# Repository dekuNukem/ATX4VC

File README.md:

# ATX4VC: ATX Power on Retro Computers!

[Buy ATX4VC](https://www.tindie.com/products/dekuNukem/atx4vc-atx-power-on-retro-computers/) | [Discord](https://discord.gg/T9uuFudg7j) | [User Manual](#user-manual) | [Table of Contents](#Table-of-Contents)

ATX4VC lets you **use ATX power supply on vintage computers**.

* Plug in ATX PSU on one end
* Get 12V, 5V, 3.3V, -12V, -5V out the other!

Features:

* All common voltage rails: +12V, +5V, +3.3V, -5V, -12V.
	* Also `5V Standby` and `Power-Good`
* Toolless Lever-Actuated Terminal Block
* USB-C Power Output
* 2x PC Fan Headers

You can use ATX4VC to:

* Replace retro computer PSUs
* Test and diagnose vintage hardware
* As general-purpose multi-voltage bench PSU

## Get ATX4VC

[Click me to get one!](https://www.tindie.com/products/dekuNukem/atx4vc-atx-power-on-retro-computers/)

## PicoRC

Also [check out PicoRC](https://picorc.com) for **device-specific** and **lower-cost** PicoPSU adaptors.

## Showcase

Here ATX4VC replaces the dead PSU in my IBM 5155 Portable PC, providing +12, +5, -12, and -5V.

Note the significant simplification and space/weight saving.

It also works as a **multi-voltage bench PSU** for testing and diagnostics.

Here it powers a Macintosh Plus motherboard with +12, +5, and -12V.

## Why

Power supplies are a major failure point of old computers today.

Those early PSUs are heavy, inefficient, and (slightly) explosive! After 40 odd years, many are not working, or worse might cause damage with out-of-spec voltages.

ATX4VC is designed to replace them with much more reliable modern ATX PSUs, and help test and diagnose vintage computers.

## User Manual

### ATX vs Pico PSU

ATX4VC works with **any ATX PSU**.

Although for **permanent retrofitting**, a **PicoPSU** is recommended due to its compact size.

* [Official website](https://www.mini-box.com/DC-DC) and [distributors](https://www.mini-box.com/site/resellers.html)
    * The cheapest **80W** one should be plenty for most
    * The **160W** variant is recommended if using many expansion cards and/or **spinning hard drive**
* Avoid **generic clones**
    * They over-rate and are of low quality
* A power brick with **12V DC** and **center positive** 5.5x2.5mm barrel jack is also needed.
    * They are very popular and you might already have one
    * Make sure it has enough wattage

### Quick Start

* Don't connect any load yet!

1. Plug in ATX connector
2. On **Power Mode** switch, select **Soft Power** (left position).
3. Press the button

PSU should turn on, voltage rail LEDs should light up. 

That's the gist of it! **Please do keep reading** for more info.

### Power Modes

* Soft Power
    * **Short press** once to turn on
    * Short press again to turn off
    * Suitable for **momentary push buttons**
* Hard Power
    * **Hold down** to power on
    * **Release** to power off
    * Suitable for **latching buttons / flip switches**
    * Connected directly to ATX **PS_ON** Signal

### External Power Button and Power LED

You can also attach an **external power button** and **power LED** to the headers below:

* Note LED polarity
* LED header has built-in **330 Ohm** resistor 
* Select suitable power mode
    * Soft Power: Momentary Pushbuttons
    * Hard Power: Latching Buttons / Flip Switches

### Power Connection

* See photo for power rails
    * For aux output harness, use **8P JST VH 3.96** female connector.
* 5VSB = 5V Standby
    * Available even when PSU is off
* Power Good Signal
    * 5V when all rails are stable
    * 0V otherwise

To connect a wire:

* Strip the insulation about 12mm / 0.5in.
* Lift handle, insert, push back down.

Also, make sure the conductor is thick enough!

Label the rails, vinyl stickers are available on the [product page](https://www.tindie.com/products/dekuNukem/atx4vc-atx-power-on-retro-computers/):

### Pre-flight Checks

Before powering up:

* Double check the **correct voltage terminal** is used
* Check for **dead shorts** between each voltage rail and GND, and between themselves!

Once powered up:

* Check voltage readings on each rail

Remember that ATX4VC **DOES NOT** monitor or condition voltage rails, so ensure the PSU itself is of good quality and trustworthy!

### Current Limit

* **`5 AMPS MAX`** OVER **ANY SINGLE RAIL**
* **`7 AMPS MAX`** **TOTAL CURRENT** OVER ALL RAILS

If more is needed, **tap the power directly** from a Molex connector.

See your PSU label or datasheet to see how much current it can provide:

### Fuses

* USE FUSES RATED **5A OR LESS**
* **DO NOT BYPASS FUSES**

ATX4VC uses common **automotive fuses**.

Regular, Mini, and Low-profile Mini all work.

Simply push into the holder.

### Fan Headers

Two PC Fan headers are available. You can plug in any regular **12V PC fan**, both 3-Pin and 4-Pin.

### USB-C Power Output

An USB-C port is available for **powering external devices**.

* **OUTPUT ONLY**, **DO NOT BACKFEED** with another powered device.

## Questions or Comments?

Feel free to ask in official [Discord Chatroom](https://discord.gg/T9uuFudg7j), raise a [Github issue](https://github.com/dekuNukem/ATX4VC/issues), or email `dekunukem` `gmail.com`!

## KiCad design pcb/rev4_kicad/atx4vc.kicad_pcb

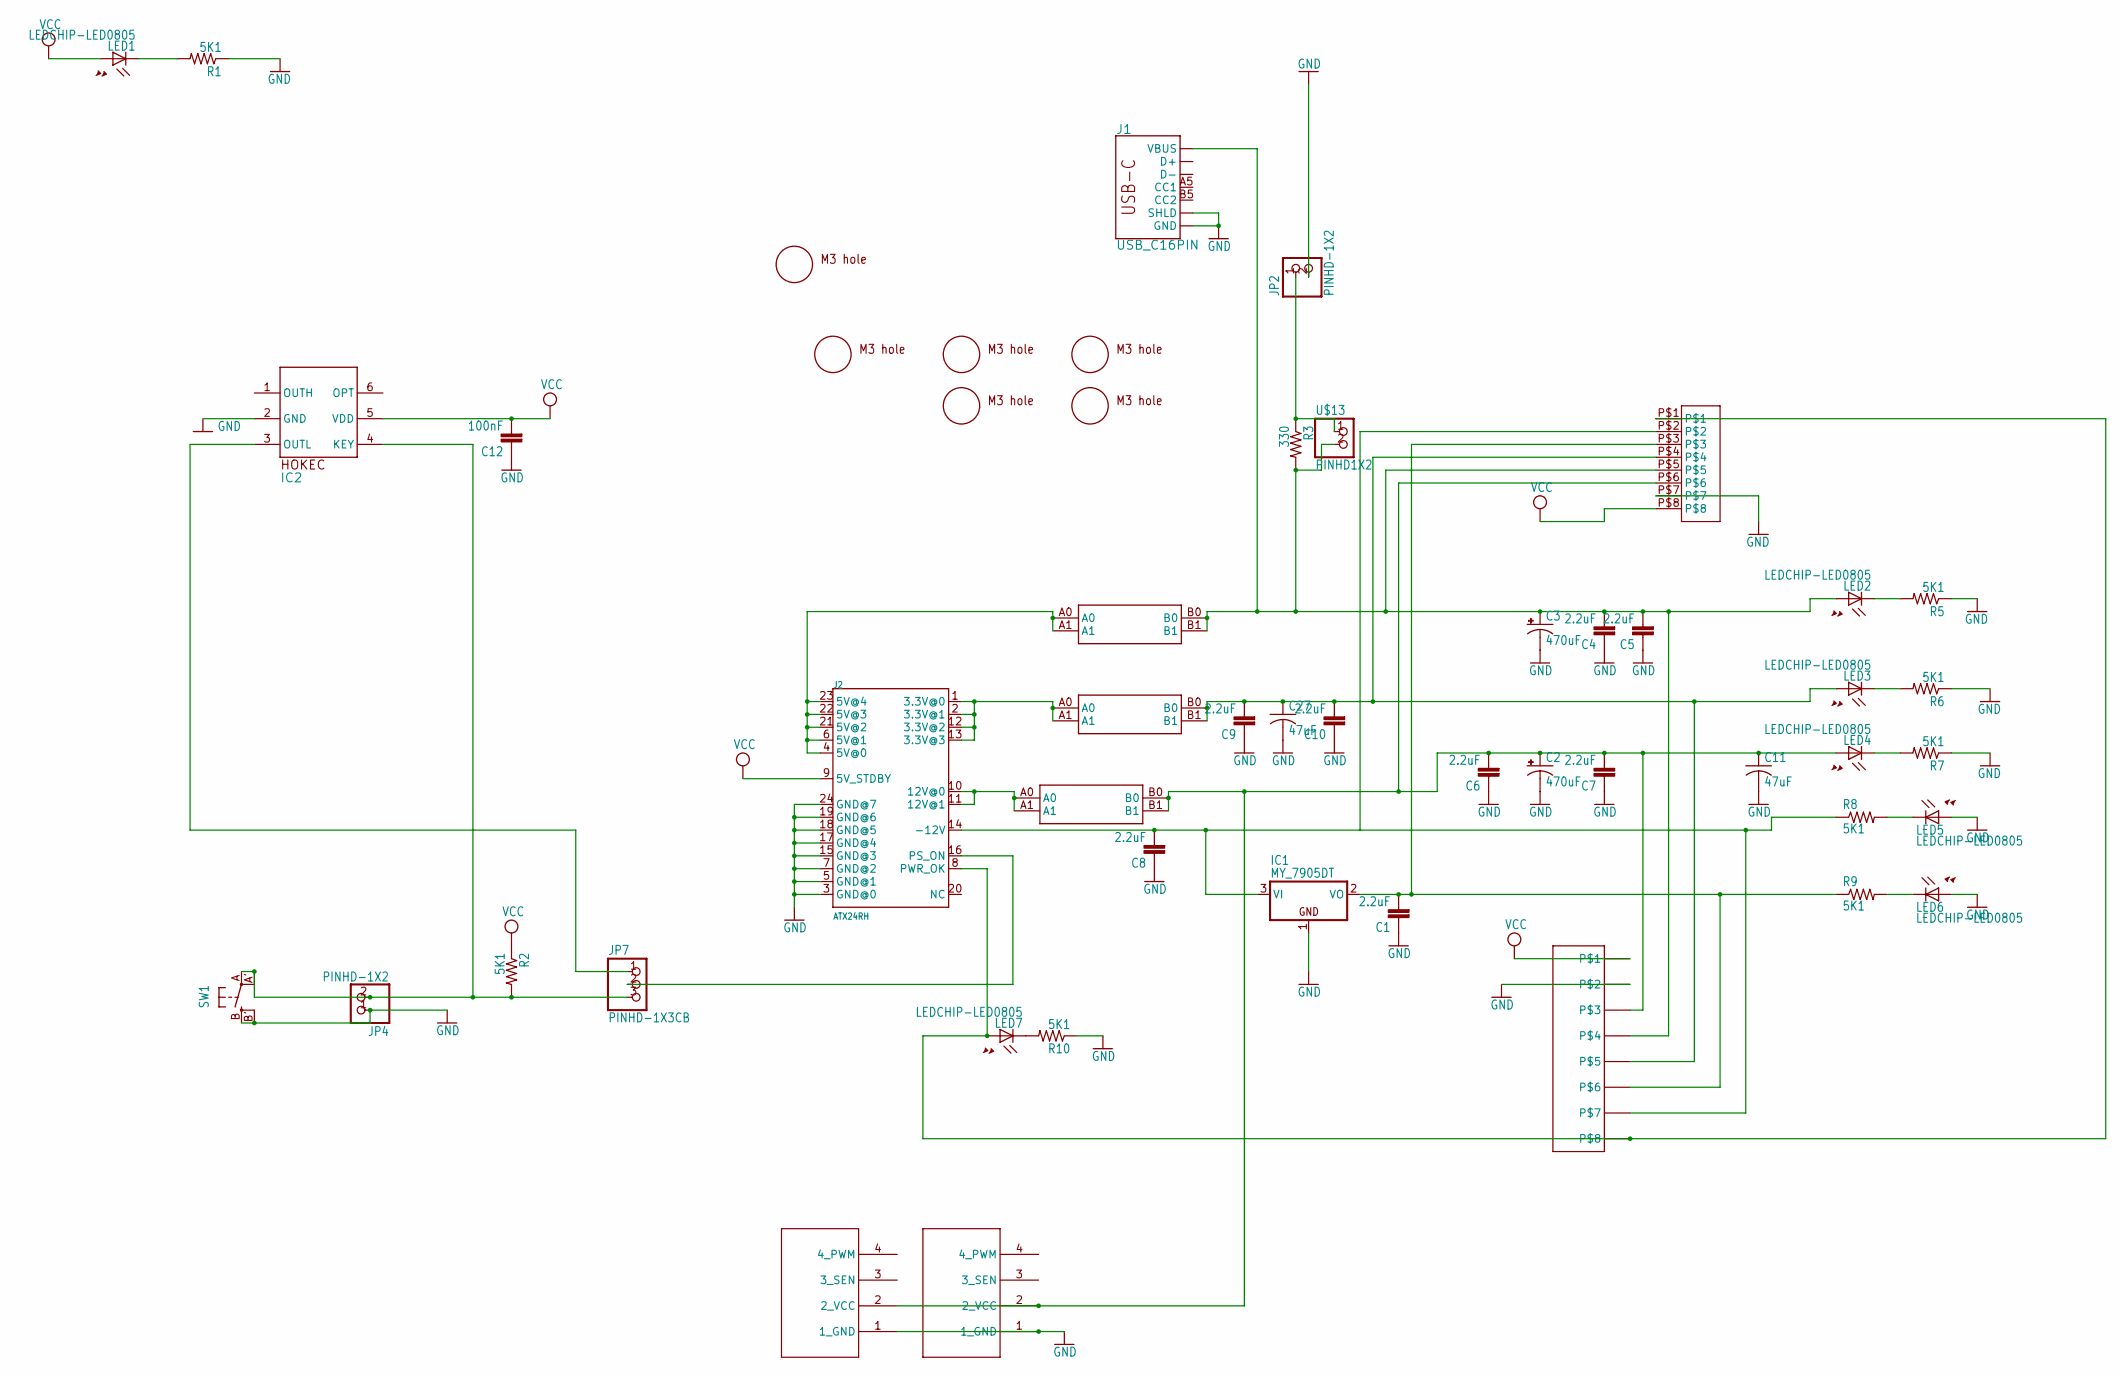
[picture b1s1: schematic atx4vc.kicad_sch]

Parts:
C1, C4, C5, C6, C7, C8, C9, C10: 2.2uF; 0805$1
C2, C3: 470uF; SMC_D
C11, C27: 47uF; C1210
C12: 100nF; 0805$1
IC1: MY_7905DT; ADAFRUIT_TO252
IC2: MAX486X/SOT; SOT23-6
J1: USB_C16PIN; USB-C-16P
J2: ATX24RH; ATX24_RIGHT_ANGLE
JP1, JP5: 4PIN_FAN; 1X04
JP2, JP4: PINHD-1X2; 1X02
JP7: PINHD-1X3CB; 1X03-CLEANBIG
LED1, LED2, LED3, LED4, LED5, LED6, LED7: LEDCHIP-LED0805; CHIP-LED0805
R1, R2, R5, R6, R7, R8, R9, R10: 5K1; 0805
R3: 330; 0805
SW1: SPST_TACT-EVQQ2; EVQ-Q2
U$1, U$2, U$3, U$4, U$5, U$6: M3_MOUNTING_HOLE; M3_MOUNTING_HOLE_PACK
U$7: 396_CONN_VH396_8P; 396_CONN_396_8P
U$9, U$10, U$11: CAR_FUSE_HOLDER3IN1; FUSE_HOLDER_3IN1
U$12: DG2204R-5.0-8DG2204-8; DG2204R-8
U$13: PINHD1X2; 1X02

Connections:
GND: C1.1, C2.-, C3.-, C4.1, C5.1, C6.1, C7.1, C8.1, C9.1, C10.1, C11.2, C12.1, C27.2, IC1.1 (GND), IC2.2 (GND), J1.GND, J1.GND2 (GND), J1.SHLD1 (SHLD), J1.SHLD2 (SHLD), J1.SHLD3 (SHLD), J1.SHLD4 (SHLD), J1.SHLD5 (SHLD), J1.SHLD6 (SHLD), J1.SHLD7 (SHLD), J1.SHLD8 (SHLD), J2.3 (GND@0), J2.5 (GND@1), J2.7 (GND@2), J2.15 (GND@3), J2.17 (GND@4), J2.18 (GND@5), J2.19 (GND@6), J2.24 (GND@7), JP1.1 (1_GND), JP2.2, JP4.1, JP5.1 (1_GND), LED5.A, LED6.A, R1.1, R5.1, R6.1, R7.1, R10.1, SW1.B (S), SW1.B' (S1), U$7.P$7, U$12.P$3, U$12.P$4
unnamed: C3.+, C4.2, C5.2, J1.VBUS1 (VBUS), J1.VBUS2 (VBUS), LED2.A, R3.2, U$7.P$5, U$9.B0, U$9.B1, U$12.P$7, U$12.P$8, U$13.2
unnamed: C9.2, C10.2, C27.1, LED3.A, U$7.P$4, U$10.B0, U$10.B1, U$12.P$9, U$12.P$10
unnamed: C8.2, IC1.3 (VI), J2.14 (-12V), R8.1, U$7.P$2, U$12.P$13, U$12.P$14
unnamed: C1.2, IC1.2 (VO), R9.1, U$7.P$3, U$12.P$11, U$12.P$12
unnamed: IC2.4 (KEY), JP4.2, JP7.3, R2.2, SW1.A, SW1.A' (P1)
unnamed: IC2.3 (OUTL), JP7.1
unnamed: J1.A6 (D+), J1.B6 (D+)
unnamed: J1.A7 (D-), J1.B7 (D-)
unnamed: J2.1 (3.3V@0), J2.2 (3.3V@1), J2.12 (3.3V@2), J2.13 (3.3V@3), U$10.A0, U$10.A1
unnamed: J2.4 (5V@0), J2.6 (5V@1), J2.21 (5V@2), J2.22 (5V@3), J2.23 (5V@4), U$9.A0, U$9.A1
unnamed: J2.10 (12V@0), J2.11 (12V@1), U$11.A0, U$11.A1
unnamed: J2.16 (PS_ON), JP7.2
unnamed: J2.8 (PWR_OK), LED7.A, U$7.P$1, U$12.P$15, U$12.P$16
unnamed: C2.+, C6.2, C7.2, C11.1, JP1.2 (2_VCC), JP5.2 (2_VCC), LED4.A, U$7.P$6, U$11.B0, U$11.B1, U$12.P$5, U$12.P$6
unnamed: JP2.1, R3.1, U$13.1
unnamed: LED1.C, R1.2
unnamed: LED2.C, R5.2
unnamed: LED3.C, R6.2
unnamed: LED4.C, R7.2
unnamed: LED5.C, R8.2
unnamed: LED6.C, R9.2
unnamed: LED7.C, R10.2
VCC: C12.2, IC2.5 (VDD), J2.9 (5V_STDBY), LED1.A, R2.1, U$7.P$8, U$12.P$1, U$12.P$2

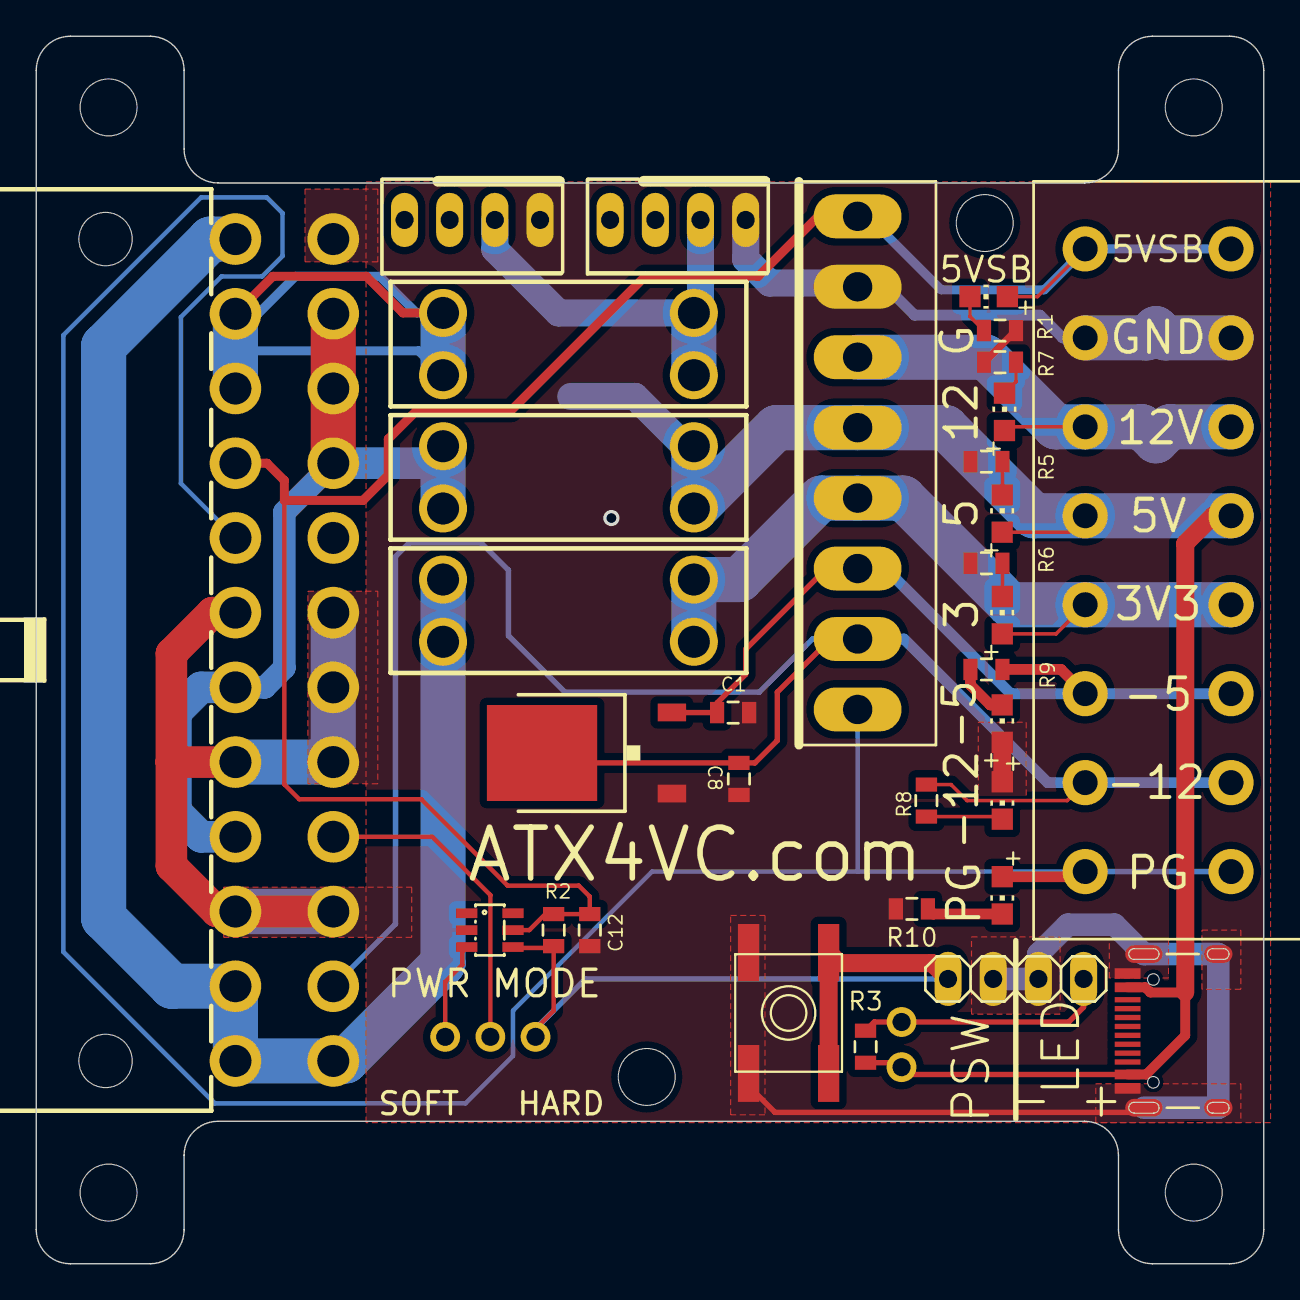
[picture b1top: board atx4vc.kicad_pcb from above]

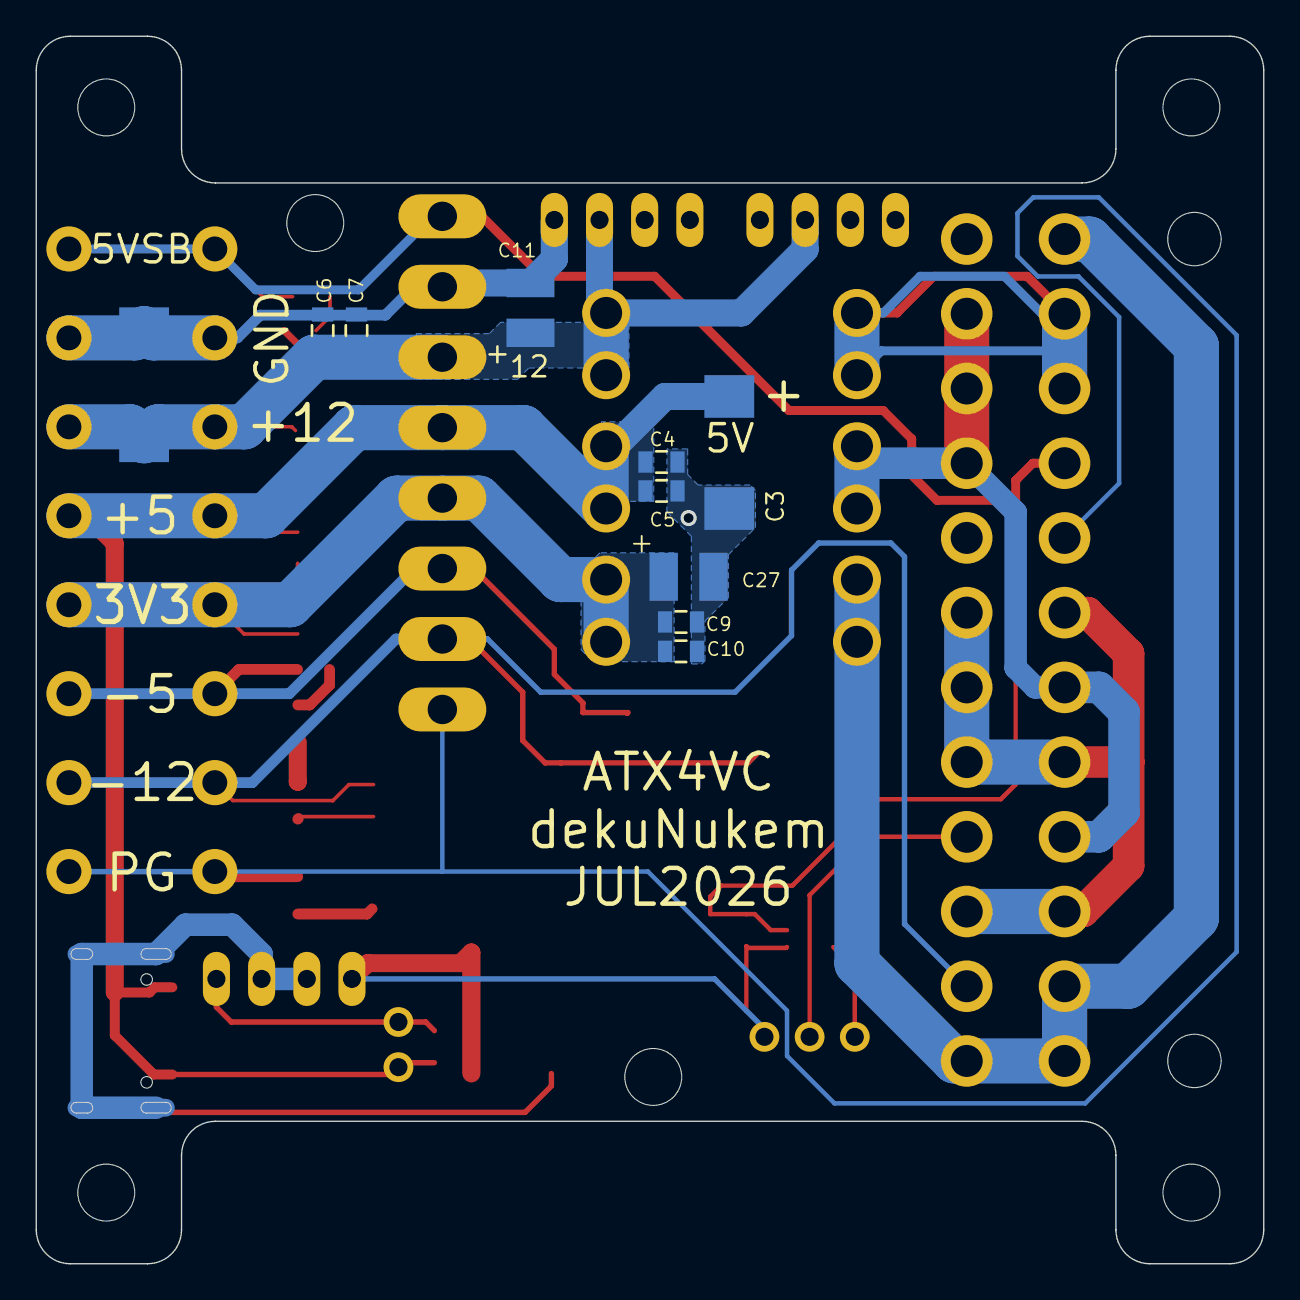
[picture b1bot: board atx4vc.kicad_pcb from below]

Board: 2 copper layers, 69.0 x 69.0 mm, 51 parts (10 on the bottom side), 24 nets.

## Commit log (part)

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2022-07-18 added plate and pcb files
2022-07-18 working on PCB
2022-07-18 pcb done sent to fab
2022-07-19 removed unneeded files
2022-07-25 adjusted pcb
2022-07-25 writing button debouncing firmware
2022-07-26 button working
2022-08-09 ws2812 working
2022-08-09 working on new ATX PCB
2022-08-10 atx board finished
2022-08-10 updated changelog, adjusted silkscreen
2022-08-14 updated atx adaptor plate, removed terminal block GND thermals
2022-08-14 updated atx board
2022-08-15 removed pot and added buttons and header
2022-08-19 updated plate
2022-08-22 making backlight PCB
2022-08-23 atx rgb done, updated atx psu board too
2022-08-23 cleaned up files
2022-08-28 added button reading and 16ms timer interupt
2022-08-30 updated pcb
2022-08-30 fixed led board silkscreen, changed ATX4VC to use PG signal
2022-08-30 added UART RX header, brightness button shared with DFU button
2022-08-30 fan pwm working
2022-08-30 rgb led working
2022-08-31 button read working
2022-08-31 optimised RGB LED write to reduce RAM usage
2022-08-31 button count working
2022-08-31 eeprom working
2022-08-31 cleaned up code
2022-08-31 adjusted fuse holder on PCB
2022-08-31 fan speed step done
2022-08-31 before testing iwdg
2022-08-31 added pwr_good check on boot
2022-08-31 updated pcb headers
2022-08-31 added hsv to rgb conversion
2022-08-31 added color and brightness adjustment
2022-09-01 station rainbow working
2022-09-01 added rolling rainbow and crossfade
2022-09-01 working on breathing led
2022-09-01 breathing led done
2022-09-01 added compatibilty with flip switch power
2022-09-01 added button autorepeat
2022-09-01 adjust brightness scale
2022-09-01 added idwg
2022-09-01 added selector jumper for power-on detect
2022-09-01 cleanup
2022-09-01 adjusted power button and power LED
2022-09-03 optimised traces routing for current carrying
2022-09-03 minor cleanup
2022-09-03 updated PCB to use car fuse holder
2022-09-03 moved bbc files to its own repo
2022-09-03 added readme
2022-09-04 added dual fan and ARGB headers, ready for new run
2022-09-09 fixed fuse holder footprint
2022-09-22 troubleshooting coolermaster RGB bug
2022-09-22 adjusted ARGB timing
2022-09-22 added ds18b20 header
2022-09-22 ds18b20 working
2022-09-22 added indicator LED
2022-09-22 adjusted LED resistor value, optimised GND plane
2022-09-26 moved ARGB header, removed GND thermals, jumper pad on USBC data lines, finishing touches
2022-09-26 wired to softpower by default
2022-09-26 pretty much done
2022-09-27 added cafe readme
2022-09-27 changed to current name
2022-09-29 added new rolling dim animation, fixing a bug
2022-09-29 fixed interrupt latency bug
2022-09-30 working on power-up fade in
2022-09-30 added startup-fadein
2022-09-30 optimising rolling dim
2022-09-30 added startup fadein in rolling dim
2022-09-30 fixed animation timing issue
2022-09-30 fixed a bug
2022-09-30 fixed power up animation detect
2022-09-30 fixed power up fade in timing
2022-10-05 writing
2022-10-05 pretty much ready
2022-10-05 added table of contents
2022-10-07 added user LED feedback and adjusted button debouncing
2022-10-07 refined hard power support
2022-10-08 added ds18b20 read
2022-10-08 added 50C fan curve
2022-10-08 fan curve feature added, working on blinking lights
2022-10-08 fan curve and light blink done
2022-10-08 adjusted blink brightness
2022-10-11 moved argb header to make more room
2022-10-11 cleaned up PCB
2022-10-11 more concise wording
2022-10-20 updated instructions
2022-10-20 added dfu file
2022-10-30 added sticker label template
2022-10-30 added sticker photo
2022-11-07 added sticker instruction
2022-11-09 working on mac plus adaptor
2022-11-09 mac plus adaptor pretty much done
2022-11-11 working on mac SE adaptor
2022-11-11 mac SE adaptor done
2022-11-11 added mac SE power board
2022-11-11 getting ready for a PCB run
2022-11-12 added more photos
2022-11-14 clean up wording
2022-11-19 adding power connector and fuse detect
2022-11-22 updated doc
2022-11-23 updated mac plus atx adaptor
2022-11-24 updating mac SE atx adaptor
2022-11-24 updated mac SE pcb
2022-11-24 finishing touches
2022-11-24 updated switch footprint
2022-11-25 added appleii
2022-11-25 working on appleii
2022-11-26 updated silkscreen and switched to terminal block for power input
2022-12-02 updated se board
2022-12-05 adding device-specifc doc
2022-12-06 changed name to ATX4VC Pico
2022-12-06 working on doc
2022-12-10 writing idoc
2022-12-10 writing docs
2022-12-10 added toc
2022-12-11 getting ready for tindie listing
2022-12-12 moved picoPSU adaptor to its own repo at PicoRC
2022-12-13 updated flip switch footprint
2022-12-19 updated library
2023-02-21 mentions picoRC
2023-03-09 updated fuse detect chip trace
2023-03-09 added datasheet
2023-03-09 switched to WAGO connectors
2023-03-09 moved ARGB header
2023-03-09 adjusted ARGB header
2023-03-27 working on seperate MCU version
2023-03-27 working on daughterboard
2023-04-03 updated instruction
2023-04-03 working on new version
2023-04-04 new daughterboard
2023-04-05 cleaned up traces
2023-04-05 added edgepad
2023-04-06 updated lbr
2023-04-06 added 5VSB to terminal block, cleaned up files
2023-04-07 updated silkscreen
2023-04-07 added information about new revision
2023-04-11 adjusted fuse position
2023-04-11 fixed a wrong signal
2023-04-11 added pullup on 1wire, gnd pour cleanup
2023-04-11 moved pin headers to the outer edge
2023-04-11 freed up more space
2023-04-18 finishing touches before production run
2023-05-10 updated photos for new version
2023-05-10 fix typos
2023-05-11 added MCU daughtboard instructions
2023-05-18 added PG on terminal block, moved things around
2023-06-01 adding more caps
2023-06-01 new run
2023-06-27 minor adjust
2023-08-14 adjust screw location, clean up traces
2023-11-27 added power LED resistor bypass
2023-12-27 minor adjustments for next production run
2023-12-27 equal dimension
2023-12-27 adjusted snapoff holes
2024-01-10 adjusted hole size
2024-01-11 new production run
2024-03-04 updated photos
2024-05-23 working on updates
2024-05-26 working on update
2024-06-02 rail silkscreen on bottom
2024-10-09 trying out power ic
2024-10-14 soft power ic tested working
2024-10-28 using github pages
2026-04-01 update doc
2026-06-30 added kicad version
2026-06-30 clean up kicad PCB
